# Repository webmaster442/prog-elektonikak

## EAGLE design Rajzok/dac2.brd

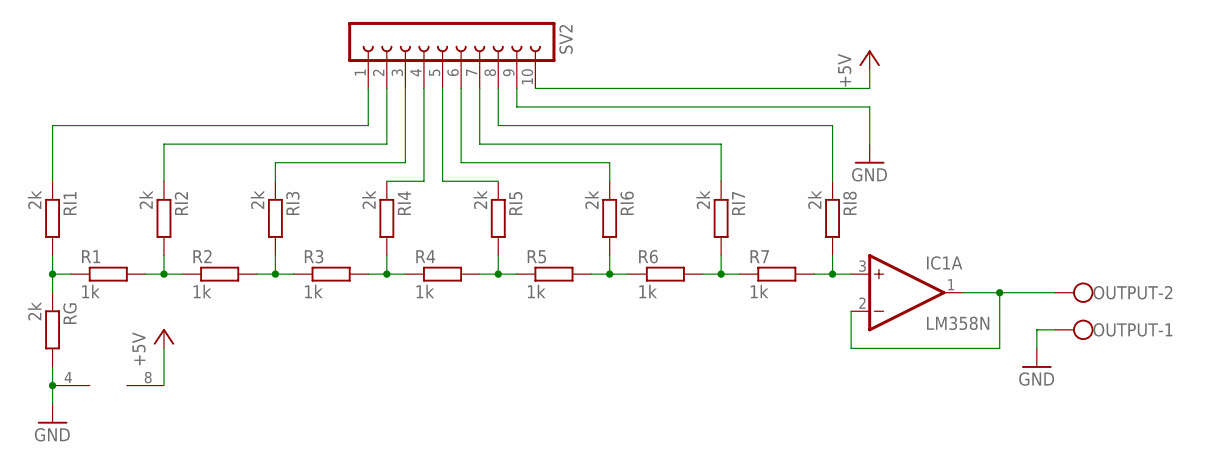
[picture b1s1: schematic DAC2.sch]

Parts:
IC1: LM358N; DIL08
OUTPUT: W237-102
R1, R2, R3, R4, R5, R6, R7: 1k; 0207/12
RG: 2k; 0207/12
RI1, RI2, RI3, RI4, RI5, RI6, RI7, RI8: 2k; 0207/12
SV2: FE10-1; FE10

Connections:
+5V: IC1.8 (V+), SV2.10
GND: IC1.4 (V-), OUTPUT.1, RG.2, SV2.9
unnamed: R1.1, RG.1, RI1.2
unnamed: R1.2, R2.1, RI2.2
unnamed: R2.2, R3.1, RI3.2
unnamed: R3.2, R4.1, RI4.2
unnamed: R4.2, R5.1, RI5.2
unnamed: R5.2, R6.1, RI6.2
unnamed: R6.2, R7.1, RI7.2
unnamed: IC1.3 (+IN), R7.2, RI8.2
unnamed: IC1.1 (OUT), IC1.2 (-IN), OUTPUT.2
unnamed: RI1.1, SV2.1
unnamed: RI2.1, SV2.2
unnamed: RI3.1, SV2.3
unnamed: RI4.1, SV2.4
unnamed: RI5.1, SV2.5
unnamed: RI6.1, SV2.6
unnamed: RI7.1, SV2.7
unnamed: RI8.1, SV2.8

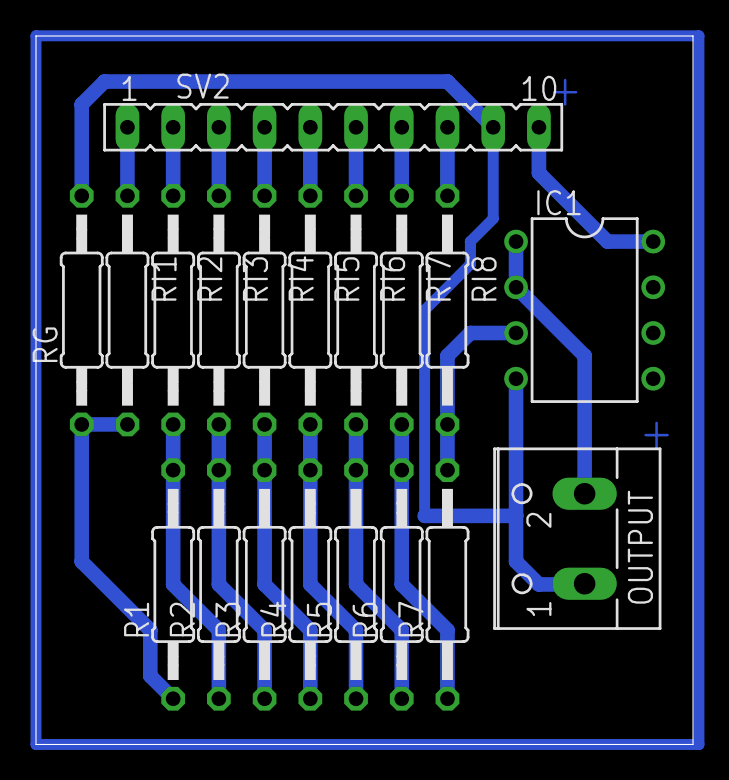
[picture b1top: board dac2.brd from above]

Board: 2 copper layers, 36.5 x 39.4 mm, 19 parts (0 on the bottom side), 19 nets.

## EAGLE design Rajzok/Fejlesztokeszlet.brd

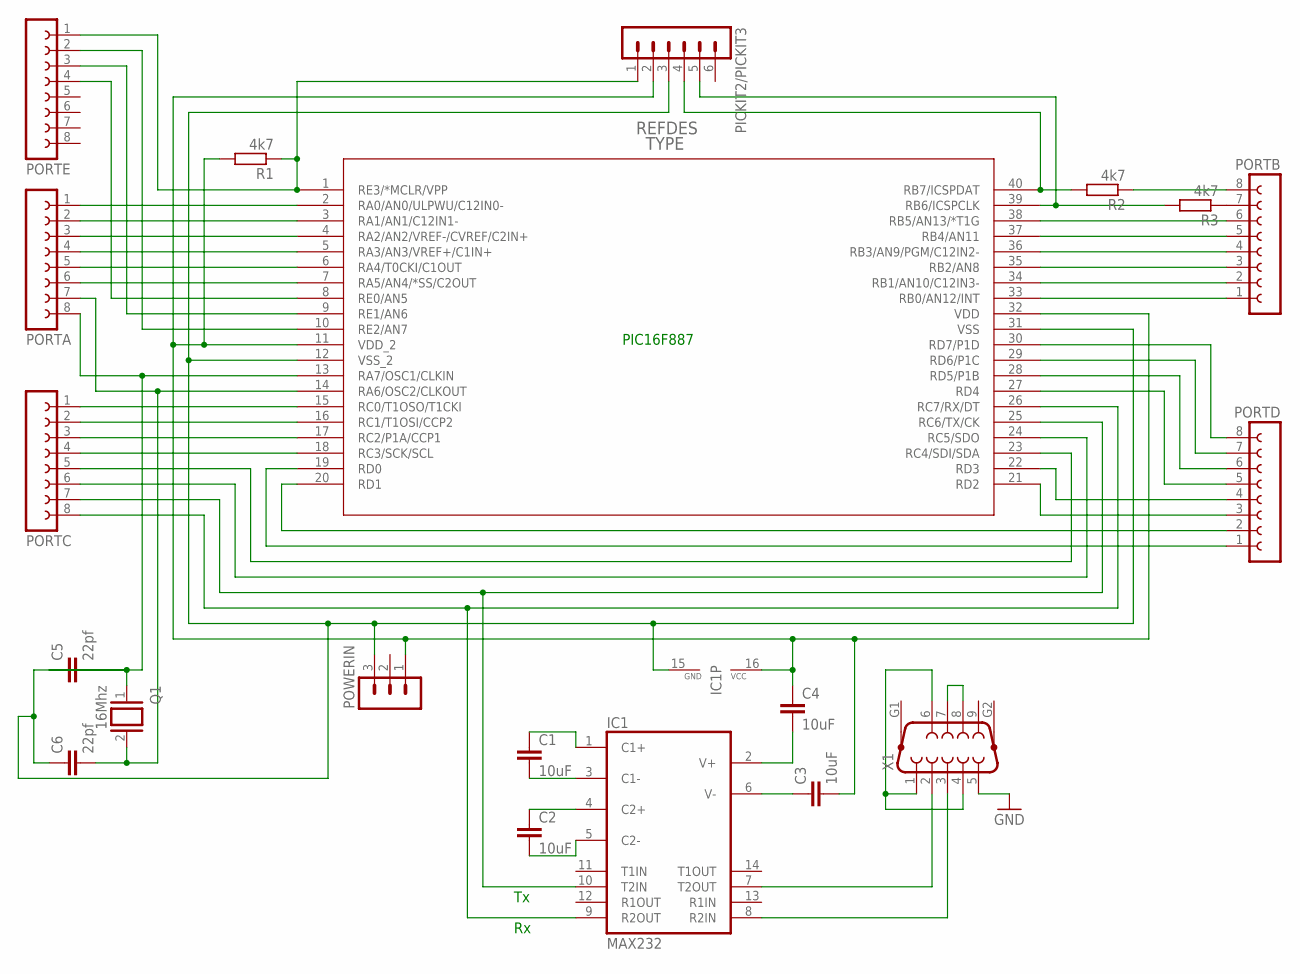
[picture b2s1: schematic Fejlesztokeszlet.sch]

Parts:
C1, C2, C3, C4: 10uF; C5B3.5
C5, C6: 22pf; C7.5B3
IC1: MAX232; DIL16
PIC16F887: PIC16F887-X/P; PDIP40_600MC
PICKIT2/PICKIT3: MA06-1
PORTA: FE08-1; FE08
PORTB: FE08-1; FE08
PORTC: FE08-1; FE08
PORTD: FE08-1; FE08
PORTE: FE08-1; FE08
POWERIN: MA03-1
Q1: 16Mhz; Q
R1, R2, R3: 4k7; 0204/7
X1: F09HP

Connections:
GND: X1.5
unnamed: PIC16F887.2 (RA0/AN0/ULPWU/C12IN0-), PORTA.1
unnamed: PIC16F887.3 (RA1/AN1/C12IN1-), PORTA.2
unnamed: PIC16F887.4 (RA2/AN2/VREF-/CVREF/C2IN+), PORTA.3
unnamed: PIC16F887.5 (RA3/AN3/VREF+/C1IN+), PORTA.4
unnamed: PIC16F887.6 (RA4/T0CKI/C1OUT), PORTA.5
unnamed: PIC16F887.7 (RA5/AN4/*SS/C2OUT), PORTA.6
unnamed: C6.2, PIC16F887.14 (RA6/OSC2/CLKOUT), PORTA.7, Q1.2
unnamed: PIC16F887.13 (RA7/OSC1/CLKIN), PORTA.8
unnamed: PIC16F887.20 (RD1), PORTD.2
unnamed: PIC16F887.19 (RD0), PORTD.1
unnamed: PIC16F887.18 (RC3/SCK/SCL), PORTC.4
unnamed: PIC16F887.17 (RC2/P1A/CCP1), PORTC.3
unnamed: PIC16F887.16 (RC1/T1OSI/CCP2), PORTC.2
unnamed: PIC16F887.15 (RC0/T1OSO/T1CKI), PORTC.1
unnamed: PIC16F887.21 (RD2), PORTD.3
unnamed: PIC16F887.22 (RD3), PORTD.4
unnamed: PIC16F887.28 (RD5/P1B), PORTD.6
unnamed: PIC16F887.27 (RD4), PORTD.5
unnamed: PIC16F887.29 (RD6/P1C), PORTD.7
unnamed: PIC16F887.30 (RD7/P1D), PORTD.8
unnamed: PIC16F887.23 (RC4/SDI/SDA), PORTC.5
unnamed: PIC16F887.24 (RC5/SDO), PORTC.6
unnamed: IC1.10 (T2IN), PIC16F887.25 (RC6/TX/CK), PORTC.7
unnamed: IC1.9 (R2OUT), PIC16F887.26 (RC7/RX/DT), PORTC.8
unnamed: PIC16F887.33 (RB0/AN12/INT), PORTB.1
unnamed: PIC16F887.34 (RB1/AN10/C12IN3-), PORTB.2
unnamed: PIC16F887.35 (RB2/AN8), PORTB.3
unnamed: PIC16F887.36 (RB3/AN9/PGM/C12IN2-), PORTB.4
unnamed: PIC16F887.37 (RB4/AN11), PORTB.5
unnamed: PIC16F887.38 (RB5/AN13/*T1G), PORTB.6
unnamed: PIC16F887.39 (RB6/ICSPCLK), PICKIT2/PICKIT3.5, R3.2
unnamed: PIC16F887.40 (RB7/ICSPDAT), PICKIT2/PICKIT3.4, R2.2
unnamed: PIC16F887.8 (RE0/AN5), PORTE.4
unnamed: PIC16F887.9 (RE1/AN6), PORTE.3
unnamed: PIC16F887.10 (RE2/AN7), PORTE.2
unnamed: PIC16F887.1 (RE3/*MCLR/VPP), PICKIT2/PICKIT3.1, PORTE.1, R1.1
unnamed: C5.1, C6.1, IC1.15 (GND), PIC16F887.12 (VSS_2), PIC16F887.31 (VSS), PICKIT2/PICKIT3.3, POWERIN.3
unnamed: C2.2, IC1.5 (C2-)
unnamed: C1.1, IC1.1 (C1+)
unnamed: C1.2, IC1.3 (C1-)
unnamed: C2.1, IC1.4 (C2+)
unnamed: C3.2, C4.1, IC1.16 (VCC), PIC16F887.11 (VDD_2), PIC16F887.32 (VDD), PICKIT2/PICKIT3.2, POWERIN.1, R1.2
unnamed: C3.1, IC1.6 (V-)
unnamed: C4.2, IC1.2 (V+)
unnamed: C5.2, Q1.1
unnamed: PORTB.8, R2.1
unnamed: X1.1, X1.4, X1.6
unnamed: X1.7, X1.8
unnamed: IC1.8 (R2IN), X1.3
unnamed: IC1.7 (T2OUT), X1.2
unnamed: PORTB.7, R3.1

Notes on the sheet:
PIC16F887

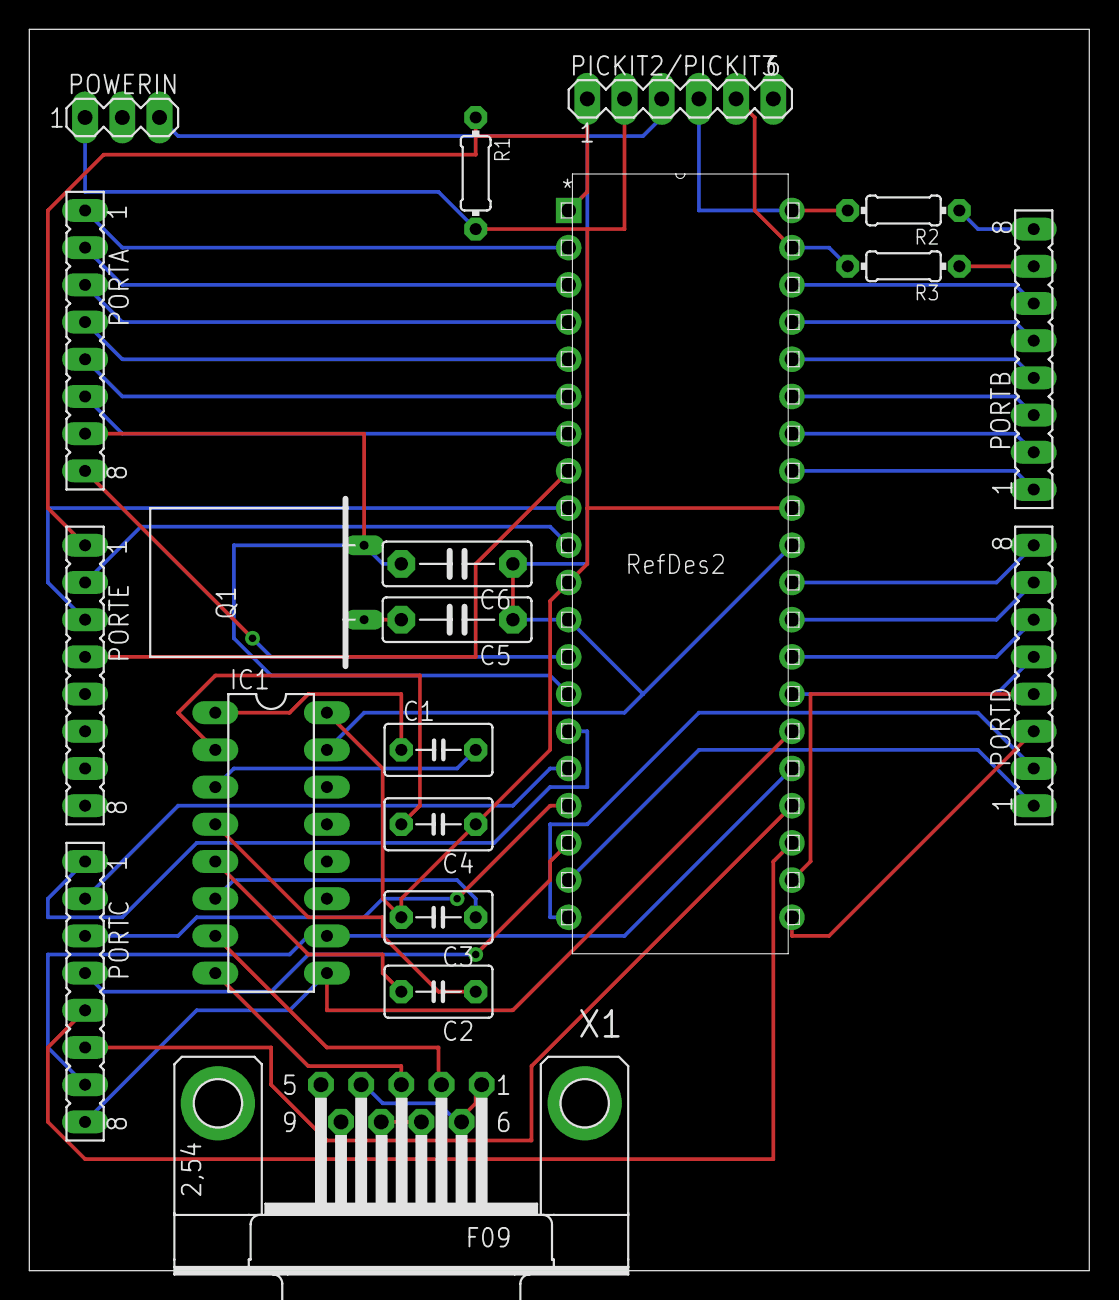
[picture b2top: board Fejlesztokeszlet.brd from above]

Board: 2 copper layers, 72.4 x 84.8 mm, 20 parts (0 on the bottom side), 51 nets.

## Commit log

2015-10-31 Melléklet fájlok v.1.0
2017-05-19 Rajzok 2017
2017-05-19 Konyvtar 2017
2017-05-19 Kódok 2017
2017-05-19 Frissítés 2017
2019-12-15 2019. változat kódjai
